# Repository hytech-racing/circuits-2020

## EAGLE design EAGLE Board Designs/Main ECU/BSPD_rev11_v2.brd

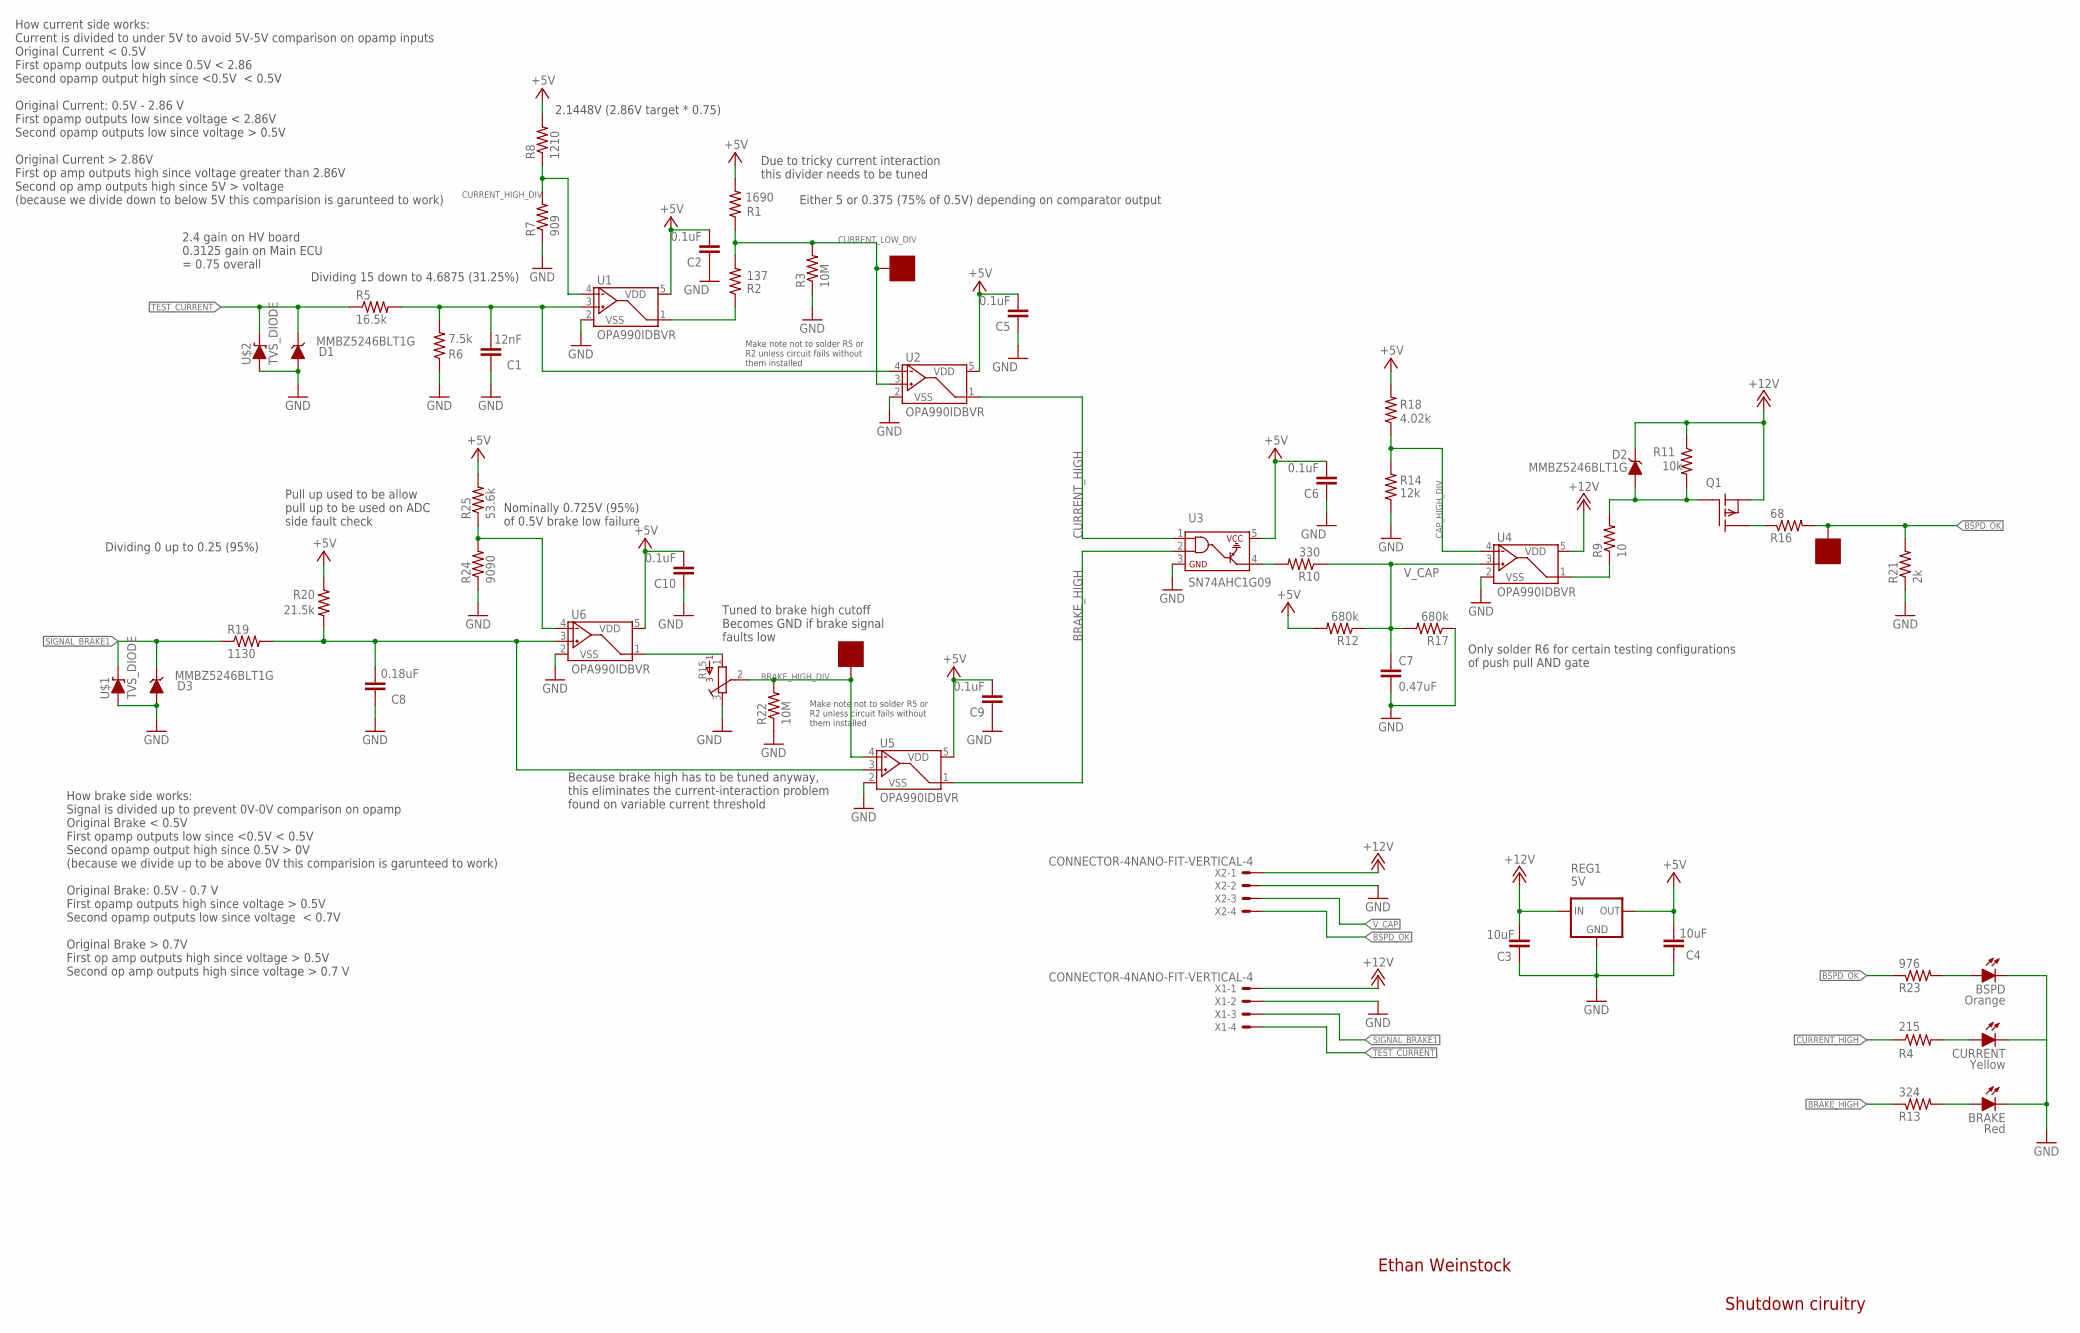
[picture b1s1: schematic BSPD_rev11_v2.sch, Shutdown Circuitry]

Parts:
BRAKE: Red; LED-603
BRAKE_LOW_DIV: SOLDER_PAD; SOLDER_PAD_XSMALL
BSPD: Orange; LED-603
BSPD_OK: SOLDER_PAD; SOLDER_PAD_XSMALL
C1: 12nF; 0603-CAP
C2, C5, C6, C9, C10: 0.1uF; 0603-CAP
C3, C4: 10uF; 0603-CAP
C7: 0.47uF; 0603-CAP
C8: 0.18uF; 0603-CAP
CURRENT: Yellow; LED-603
CURRENT_LOW_DIV: SOLDER_PAD; SOLDER_PAD_XSMALL
D1, D2, D3: MMBZ5246BLT1G; SOT23
Q1: P-CHANNEL_MOSFET_DMP3099L-7; SOT23
R1: 1690; 0603-RES
R2: 137; 0603-RES
R3, R22: 10M; 0603-RES
R4: 215; 0603-RES
R5: 16.5k; 0603-RES
R6: 7.5k; 0603-RES
R7: 909; 0603-RES
R8: 1210; 0603-RES
R9: 10; 0603-RES
R10: 330; 0603-RES
R11: 10k; 0603-RES
R12, R17: 680k; 0603-RES
R13: 324; 0603-RES
R14: 12k; 0603-RES
R15: TRIMPOT_3296C; TRIMPOT_3296
R16: 68; 0603-RES
R18: 4.02k; 0603-RES
R19: 1130; 0603-RES
R20: 21.5k; 0603-RES
R21: 2k; 0603-RES
R23: 976; 0603-RES
R24: 9090; 0603-RES
R25: 53.6k; 0603-RES
REG1: 5V; OKI-78SR
U1, U2, U4, U5, U6: OPA990IDBVR; SOT-23-5
U3: SN74AHC1G09; SOT-23-5
U$1, U$2: TVS_DIODE; U-DFN1608-2
X1, X2: CONNECTOR-4NANO-FIT-VERTICAL-4; NANO-FIT_VERTICAL-4

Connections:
+5V: C2.2, C4.2, C5.2, C6.2, C9.2, C10.2, R1.2, R8.2, R12.2, R18.2, R20.1, R25.2, REG1.3 (OUT), U1.5 (VDD), U2.5 (VDD), U3.5, U5.5 (VDD), U6.5 (VDD)
+12V: C3.2, D2.3 (C), Q1.2 (S), R11.1, REG1.1 (IN), U4.5 (VDD), X1.P$1, X2.P$1
BRAKE_HIGH: R13.1, U3.2, U5.1 (VOUT)
BRAKE_HIGH_DIV: BRAKE_LOW_DIV.P$1, R15.2, R22.2, U5.4 (VIN-)
BSPD_OK: BSPD_OK.P$1, R16.2, R21.2, R23.1, X2.P$4
CAP_HIGH_DIV: R14.2, R18.1, U4.4 (VIN-)
CURRENT_HIGH: R4.1, U2.1 (VOUT), U3.1
CURRENT_HIGH_DIV: R7.2, R8.1, U1.4 (VIN-)
CURRENT_LOW_DIV: CURRENT_LOW_DIV.P$1, R1.1, R2.2, R3.2, U2.3 (VIN+)
GND: BRAKE.C, BSPD.C, C1.1, C2.1, C3.1, C4.1, C5.1, C6.1, C7.2, C8.1, C9.1, C10.1, CURRENT.C, D1.1 (A), D3.1 (A), R3.1, R6.1, R7.1, R14.1, R15.3, R17.1, R21.1, R22.1, R24.1, REG1.2 (GND), U1.2 (VSS), U2.2 (VSS), U3.3, U4.2 (VSS), U5.2 (VSS), U6.2 (VSS), U$1.P$1 (A), U$2.P$1 (A), X1.P$2, X2.P$2
unnamed: Q1.3 (D), R16.1
unnamed: R15.1, U6.1 (VOUT)
unnamed: R9.1, U4.1 (VOUT)
unnamed: C8.2, R19.2, R20.2, U5.3 (VIN+), U6.3 (VIN+)
unnamed: R24.2, R25.1, U6.4 (VIN-)
unnamed: R2.1, U1.1 (VOUT)
unnamed: CURRENT.A, R4.2
unnamed: BRAKE.A, R13.2
unnamed: C1.2, R5.2, R6.2, U1.3 (VIN+), U2.4 (VIN-)
unnamed: R10.2, U3.4
unnamed: BSPD.A, R23.2
unnamed: D2.1 (A), Q1.1 (G), R9.2, R11.2
SIGNAL_BRAKE1: D3.3 (C), R19.1, U$1.P$2 (C), X1.P$3
TEST_CURRENT: D1.3 (C), R5.1, U$2.P$2 (C), X1.P$4
V_CAP: C7.1, R10.1, R12.1, R17.2, U4.3 (VIN+), X2.P$3

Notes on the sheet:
Ethan Weinstock
Shutdown ciruitry
Dividing 15 down to 4.6875 (31.25%)
Either 5 or 0.375 (75% of 0.5V) depending on comparator output
2.1448V (2.86V target * 0.75)
Tuned to brake high cutoff Becomes GND if brake signal faults low
Nominally 0.725V (95%) of 0.5V brake low failure
Dividing 0 up to 0.25 (95%)
2.4 gain on HV board 0.3125 gain on Main ECU = 0.75 overall
Make note not to solder R5 or R2 unless circuit fails without them installed
How current side works: Current is divided to under 5V to avoid 5V-5V comparison on opamp inputs Original Current < 0.5V First opamp outputs low since 0.5V < 2.86 Second opamp output high since <0.5V < 0.5V Original Current: 0.5V - 2.86 V First opamp outputs low since voltage < 2.86V Second opamp o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
Due to tricky current interaction this divider needs to be tuned
Pull up used to be allow pull up to be used on ADC side fault check
Because brake high has to be tuned anyway, this eliminates the current-interaction problem found on variable current threshold
How brake side works: Signal is divided up to prevent 0V-0V comparison on opamp Original Brake < 0.5V First opamp outputs low since <0.5V < 0.5V Second opamp output high since 0.5V > 0V (because we divide up to be above 0V this comparision is garunteed to work) Original Brake: 0.5V - 0.7 V First op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
Only solder R6 for certain testing configurations of push pull AND gate

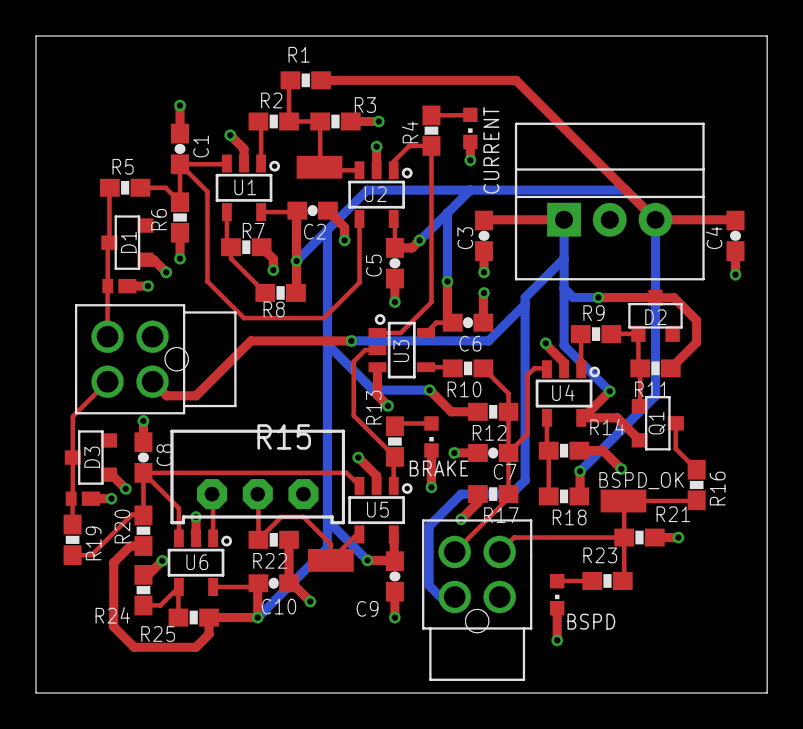
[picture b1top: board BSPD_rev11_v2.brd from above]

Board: 2 copper layers, 40.6 x 36.5 mm, 56 parts (0 on the bottom side), 25 nets.

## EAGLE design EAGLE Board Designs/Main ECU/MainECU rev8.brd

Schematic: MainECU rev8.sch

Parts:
5ABOARDFUSE, 5AFUSE, 5ASHUTDOWNFUSE: FUSE_MINIBLADE; MINI-BLADE_FUSE_HOLDER
ACC1_PD, ACC1_PU, ACC2_PD, ACC2_PU: 10k; 0805
ADXL345_BREAKOUT: M09; 1X09
BMS_SHUTDOWN_RLY: RT424012; RELAY_DPDT
BOARD_TEMP: THERMISTOR_NCP210805; 0805
BRAKE_PU: 10k; 0805
C1, C2, C20, C21: 10uF; 0805
C3, C14, C17: 1nF; 0805
C4, C12, C15, C16, C18, C19, C22, C23, C25, C26, C32, C34, C36, C43, C44, C45: .1uF; 0805
C5, C6, C11, C31, C33, C35, C37, C42: 1uF; 0805
C7, C8: 47nF; 0805
C9, C10, C30, C38, C39: 0.1uF; 0805
C13, C24: 470pF; 0805
C27, C28, C29: CAP0805; 0805
C40: 470uF; CAP-PTH-LARGE
C41: 4.7nF; 0805
CAN_TERM_JMP: M02_SLIM; 1X02_SLIM
CAN_TRANSCEIVER, CAN_TRANSCEIVER1: MCP2551; SOIC-08
D1, D2, D3, D4, D5, D6, D7, D13, D15, D16, D19, D20, D21, D22: TS4148 RYG; 0805_D
D8, D9, D10, D11, D12, D14: MMBZ5246BLT1G; SOT23
IMD_SHUTDOWN_RLY: RT424009; RELAY_DPDT
INVERTER_PWR_RELAY: G5LE; ZF112
J1, J2, J3, J4, J5, J6, J7, J8: JUMPER; 0805
LED1: White; LED-805
LED2: RED; LED-805
LED3, LED7, LED11: Green; LED-805
LED4, LED6, LED10, LED12, LED13: Red; LED-805
LED5, LED9: Yellow; LED-805
LED8: Purple; LED-805
LED14: Blue; LED-805
LED15: YELLOW; LED-805
LED16: GREEN; LED-805
MTK3339_BREAKOUT: M09; 1X09
P1, P2: SOLDER_PAD; SOLDER_PAD_XSMALL
Q9, Q11: DMG3406LSOT; SOT23
Q12: P-CHANNEL_MOSFET_DMP3099L-7; SOT23
R1, R3: 1K; 0805
R2, R4: 2K; 0805
R5, R7, R11, R15, R23, R57, R59, R61: 43k; 0805
R6, R8, R21, R22, R29, R58, R60, R62: 12k; 0805
R9, R10, R24, R27, R28, R47, R48, R53: 10k; 0805
R12, R14, R18, R55: 2k; 0805
R13, R63: 20; 0805
R16, R25, R32, R51, R52: 1.2k; 0805
R17: 20k; 0805
R20, R67, R68: 270; 0805
R30, R56: 33; 0805
R33, R34: 4.7k; 0805
R35, R36, R38, R39, R40, R41, R42, R43: 150; 0805
R37, R44, R45: 0; 0805
R46, R49: 60; 0805
R54: 5.1k; 0805
R64, R65, R66: RESISTOR0805-RES; 0805
R69: 200; 0805
REG, REG3: 5V; OKI-78SR
REG1: LM3940; SOT223
S1: BTN_10-XXSMD; TACTILE_SWITCH_SMD_6.2MM_TALL
U$1: TEENSY_3.2_SIMPLE
U$2: TEENSY_3.5_EXT
U$3: XBEE
U$4, U$6, U$7: N-CHANNEL_MOSFET_IRF1324PBF; TO-220-H-HOLE
U$5, U$19: MC34152; SOIC-08
U$8, U$11, U$12, U$14, U$15: TEST_POINT
U$9, U$10: ACS715_CURRENT_SENSOR; SOP8
U$13: CDSOT23-T24CAN-Q; SOT23
U$16: CR-2450/G1AN
U$17: MCP23S17SSOP28; SSOP28
U$18: MCP3208SOIC; SOIC-16
U$20, U$23, U$24: MCP6002SOIC; SOIC-08
U$21, U$22, U$26, U$27, U$28: MAX7480; SOIC-08
U$25: TXB0104TSSOP; TSSOP-14
U$29, U$30: TLP291-4; 11-11F1
U$31: RT424009; RELAY_DPDT
X1: CONNECTOR-37; AUTOSPORT_14-35
X2: CONNECTOR-4AUTOSPORT; AUTOSPORT_12-04
X3, X4: CONNECTOR-4NANO-FIT-VERTICAL-4; NANO-FIT_VERTICAL-4

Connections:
3.3V: R33.2, R34.2, U$2.3.3V
3.3V_MAIN_TEENSY: C44.1, U$1.3.3V, U$25.1 (VCCA), U$25.8 (OE)
12VIN: U$9.1 (IP+), U$9.2 (IP+), X2.P$1
12VSUPPLY_DIV: C37.2, R23.2, R29.1, U$23.3 (VINA+)
12VSUPPLY_READ: U$18.4 (CH3), U$23.1 (VOUTA), U$23.2 (VINA-)
12VUNFUSED: 5ABOARDFUSE.L1 (1), 5ABOARDFUSE.L2 (1), 5ASHUTDOWNFUSE.L1 (1), 5ASHUTDOWNFUSE.L2 (1), U$9.3 (IP-), U$9.4 (IP-)
+5V: ACC1_PU.2, ACC2_PU.2, BOARD_TEMP.1, BRAKE_PU.2, C2.2, C4.1, C11.2, C15.1, C18.1, C30.2, C31.2, C32.2, C33.2, C34.2, C35.1, C36.1, C38.1, C45.1, CAN_TRANSCEIVER1.3, R20.1, R54.1, REG.3 (OUT), U$1.VIN, U$11.P$1, U$17.9 (VDD), U$17.18 (!RESET), U$18.15 (VREF), U$18.16 (VDD), U$23.8 (VDD), U$24.8 (VDD), U$25.14 (VCCB), U$26.4 (VDD), U$26.7 (!SHDN), U$27.4 (VDD), U$27.7 (!SHDN), U$28.4 (VDD), U$28.7 (!SHDN), X1.P$27, X1.P$28, X1.P$29
BMS_OK_READ: R7.2, R8.1, U$18.6 (CH5)
BMS_PWR_STEP: BMS_SHUTDOWN_RLY.3, BMS_SHUTDOWN_RLY.COIL-, D5.A, D16.A
BRAKE_LIGHT: Q12.3 (D), X1.P$9
BRAKE_LIGHT_CTRL: D12.3 (C), Q11.1 (G), R10.2, U$1.D7(RX3)
CANH: CAN_TERM_JMP.1, CAN_TRANSCEIVER.7, CAN_TRANSCEIVER1.7, U$13.2, X1.P$12, X1.P$13, X3.P$4, X4.P$4
CANL: CAN_TRANSCEIVER.6, CAN_TRANSCEIVER1.6, R49.1, U$13.1, X1.P$11, X1.P$26, X3.P$3, X4.P$3
COOLINGSENSE: J5.2, R3.2, R4.2, U$20.3 (VINA+)
COOLINGSENSE_FILT: J5.1, U$2.A12, U$22.5 (OUT)
CS1_5V: U$18.10 (!CS!/SHDN), U$25.13 (B1)
CS1_TEENSY: U$1.D9(RX2), U$25.2 (A1)
CS2_5V: U$17.11 (!CS), U$25.12 (B2)
CS2_TEENSY: U$1.D10(TX2), U$25.3 (A2)
CURRENTSENSE2: C27.2, C28.2, C29.2, U$4.3 (S), U$6.3 (S), U$7.3 (S), U$10.1 (IP+), U$10.2 (IP+)
DASH11_READ: R11.2, R21.1, U$1.A0
DASH12_READ: R57.2, R58.1, U$1.A1
DASH_1_EXTERN: R44.2, X1.P$1
DASH_1_INTER: R35.1, U$17.1 (GPB0)
DASH_2_EXTERN: R37.2, X1.P$2
DASH_2_INTER: R36.1, U$17.2 (GPB1)
DASH_3_EXTERN: U$29.11 (EM3), X1.P$3
DASH_3_INTER: R38.1, U$17.3 (GPB2)
DASH_4_EXTERN: U$29.9 (EM4), X1.P$4
DASH_4_INTER: R39.1, U$17.4 (GPB3)
DASH_5_EXTERN: J1.1, U$30.15 (EM1), X1.P$18
DASH_5_INTER: J1.2, R40.1, U$17.5 (GPB4)
DASH_6_EXTERN: J2.1, U$30.13 (EM2), X1.P$19
DASH_6_INTER: J2.2, R41.1, U$17.6 (GPB5)
DASH_7_EXTERN: J3.1, U$30.11 (EM3), X1.P$20
DASH_7_INTER: J3.2, R42.1, U$17.7 (GPB6)
DASH_8_EXTERN: J4.1, U$30.9 (EM4), X1.P$21
DASH_8_INTER: J4.2, R43.1, U$17.8 (GPB7)
DASH_9_EXTERN: U$17.21 (GPA0), X1.P$23
DASH_10_EXTERN: U$17.22 (GPA1), X1.P$32
DASH_11_EXTERN: D19.A, J7.1, X1.P$6
DASH_11_INTER: J7.2, U$17.23 (GPA2)
DASH_12_EXTERN: D20.A, J8.1, X1.P$22
DASH_12_INTER: J8.2, U$17.24 (GPA3)
ECUSENSE: J6.2, R1.2, R2.2, U$20.5 (VINB+)
ECUSENSE_FILT: J6.1, U$2.A13, U$21.5 (OUT)
FAN1-: 5AFUSE.R1 (2), 5AFUSE.R2 (2), R65.1, U$7.2 (D)
FAN1CONTROL: LED4.A, U$1.A8, U$5.2 (IN_A)
FAN1DRIVE: D9.3 (C), R24.2, U$5.7 (OUT_A), U$7.1 (G)
FAN2-: R64.1, U$4.2 (D), X2.P$3
FAN2CONTROL: LED13.A, U$1.A9, U$5.4 (IN_B)
FAN2DRIVE: D8.3 (C), R28.2, U$4.1 (G), U$5.5 (OUT_B)
IMD_PWR_STEP: D6.A, D15.A, IMD_SHUTDOWN_RLY.3, IMD_SHUTDOWN_RLY.COIL-
INVERTER_CTRL: D14.3 (C), Q9.1 (G), R16.1, R47.1, U$1.D6
INVERTER_SUPPLY: INVERTER_PWR_RELAY.S, X1.P$7
LATCH_EXT_BUTTON: D13.C, D15.C, D16.C, LED1.C, S1.A1, S1.A2 (P1), X1.P$37
MISO_TEENSY: U$1.D12, U$17.14 (SO), U$18.12 (DOUT)
MOSI_5V: U$17.13 (SI), U$18.11 (DIN), U$25.10 (B4)
MOSI_TEENSY: U$1.D11, U$25.5 (A4)
MTK3339_DIN: MTK3339_BREAKOUT.6, U$2.D1(TX1)
MTK3339_DOUT: MTK3339_BREAKOUT.5, U$2.D0(RX1)
MTK3339_FIX: MTK3339_BREAKOUT.4, U$2.D2
unnamed: 5AFUSE.L1 (1), 5AFUSE.L2 (1), X1.P$17
unnamed: LED1.A, R54.2
unnamed: R1.1, U$9.7 (VIOUT)
unnamed: C12.2, U$27.1 (COM), U$27.6 (OS)
unnamed: D20.C, R57.1
unnamed: R3.1, U$10.7 (VIOUT)
unnamed: MTK3339_BREAKOUT.2, R53.2
unnamed: C8.1, U$9.6 (FILTER)
unnamed: LED3.A, R56.2
unnamed: D1.C, R5.1
unnamed: D2.C, R7.1
unnamed: CAN_TRANSCEIVER.4, U$2.D4(CANRX)
unnamed: CAN_TRANSCEIVER.1, U$2.D3(CANTX)
unnamed: CAN_TRANSCEIVER1.4, U$1.D4(CANRX)
unnamed: CAN_TERM_JMP.2, R46.2
unnamed: D19.C, R11.1
unnamed: LED5.A, R14.2
unnamed: U$20.1 (VOUTA), U$20.2 (VINA-), U$22.2 (IN)
unnamed: C3.1, U$27.8 (CLK)
unnamed: CAN_TRANSCEIVER1.1, U$1.D3(CANTX)
unnamed: U$24.1 (VOUTA), U$24.2 (VINA-), U$28.2 (IN)
unnamed: U$24.6 (VINB-), U$24.7 (VOUTB), U$27.2 (IN)
unnamed: U$23.6 (VINB-), U$23.7 (VOUTB), U$26.2 (IN)
unnamed: LED9.A, R55.2
unnamed 89: D7.A, D13.A, U$31.3, U$31.COIL-; also elsewhere on the board
unnamed: LED6.A, R16.2
unnamed: LED8.A, R20.2
unnamed: R36.2, U$29.3 (VCC2)
unnamed: D21.C, R59.1
unnamed: LED7.A, R17.2
unnamed: D3.C, R15.1
unnamed: D22.C, R61.1
unnamed: LED14.C, R45.2
unnamed: C16.2, U$28.1 (COM), U$28.6 (OS)
unnamed: C19.2, U$26.1 (COM), U$26.6 (OS)
unnamed: C14.1, U$28.8 (CLK)
unnamed: U$20.6 (VINB-), U$20.7 (VOUTB), U$21.2 (IN)
unnamed: C17.1, U$26.8 (CLK)
unnamed: R37.1, U$29.13 (EM2)
unnamed: C23.2, U$21.1 (COM), U$21.6 (OS)
unnamed: C13.1, U$21.8 (CLK)
unnamed: LED11.C, R30.2
unnamed: LED11.A, U$3.6 (PWM0/RSSI)
unnamed: C7.1, U$10.6 (FILTER)
unnamed: LED10.A, U$3.15 (ASC/AD5/DIO5)
unnamed: LED10.C, R32.2
unnamed: R35.2, U$29.1 (VCC1)
unnamed: R38.2, U$29.5 (VCC3)
unnamed: R39.2, U$29.7 (VCC4)
unnamed: R40.2, U$30.1 (VCC1)
unnamed: R41.2, U$30.3 (VCC2)
unnamed: R42.2, U$30.5 (VCC3)
unnamed: R43.2, U$30.7 (VCC4)
unnamed: D11.1 (A), Q11.3 (D), Q12.1 (G), R48.2
unnamed: R44.1, U$29.15 (EM1)
unnamed: U$2.GND_2, U$16.-
unnamed: C41.1, R46.1, R49.2
unnamed: LED14.A, U$3.20 (AD0/DIO0)
unnamed: C27.1, R64.2
unnamed: D4.A, INVERTER_PWR_RELAY.2 (COIL-), Q9.3 (D)
unnamed: C26.2, U$22.1 (COM), U$22.6 (OS)
unnamed: C24.1, U$22.8 (CLK)
unnamed: LED4.C, R25.1
unnamed: LED12.C, R51.1
unnamed: LED13.C, R52.1
unnamed: P1.P$1, U$17.25 (GPA4)
unnamed: P2.P$1, U$17.26 (GPA5)
unnamed: C28.1, R65.2
unnamed: C29.1, R66.2
unnamed: LED2.C, R67.2
unnamed: LED15.C, R68.2
unnamed: LED16.C, R69.2
OKHS_READ: R5.2, R6.1, U$18.7 (CH6)
PUMP1-: R66.1, U$6.2 (D), X2.P$2
PUMPCONTROL: LED12.A, U$1.A6, U$19.2 (IN_A)
PUMPDRIVE: D10.3 (C), R27.2, U$6.1 (G), U$19.7 (OUT_A)
READ_ACCEL1: U$18.2 (CH1), U$27.5 (OUT)
READ_ACCEL2: U$18.3 (CH2), U$28.5 (OUT)
READ_BRAKE: U$18.1 (CH0), U$26.5 (OUT)
SCK_5V: U$17.12 (SCK), U$18.13 (CLK), U$25.11 (B3)
SCK_TEENSY: U$1.D13, U$25.4 (A3)
SCL: ADXL345_BREAKOUT.9, R34.1, U$2.A5
SDA: ADXL345_BREAKOUT.8, R33.1, U$2.A4
SHUTDOWN_A: 5ASHUTDOWNFUSE.R1 (2), 5ASHUTDOWNFUSE.R2 (2), IMD_SHUTDOWN_RLY.6
SHUTDOWN_B: BMS_SHUTDOWN_RLY.6, D21.A, IMD_SHUTDOWN_RLY.5, R14.1
SHUTDOWN_B_READ: R59.2, R60.1, U$1.A2
SHUTDOWN_C: BMS_SHUTDOWN_RLY.5, D22.A, R17.1, U$31.6; also elsewhere on the board
SHUTDOWN_C_READ: R61.2, R62.1, U$1.A3
SHUTDOWN_D: D3.A, U$31.5, X1.P$5; also elsewhere on the board
SHUTDOWN_OUT_READ: R15.2, R22.1, U$18.5 (CH4)
SIGNAL_ACCEL1: ACC1_PD.1, ACC1_PU.1, U$24.5 (VINB+), X1.P$25
SIGNAL_ACCEL2: ACC2_PD.1, ACC2_PU.1, U$24.3 (VINA+), X1.P$24
SIGNAL_BRAKE: BRAKE_PU.1, U$14.P$1, U$23.5 (VINB+), X1.P$8
SOFTWARE_SHUTDOWN: D13.3, U$1.A7; also elsewhere on the board
TELEMETRY5V: ADXL345_BREAKOUT.1, C5.1, C9.1, C10.1, C21.2, C22.1, C25.1, C42.2, C43.2, CAN_TRANSCEIVER.3, MTK3339_BREAKOUT.8, R53.1, REG1.1 (IN), REG3.3 (OUT), U$2.VIN, U$9.8 (VCC), U$10.8 (VCC), U$20.8 (VDD), U$21.4 (VDD), U$21.7 (!SHDN), U$22.4 (VDD), U$22.7 (!SHDN)
TEMPSENSE: BOARD_TEMP.2, R9.2, U$18.8 (CH7)
VBAT_RTC: MTK3339_BREAKOUT.3, U$2.VBAT, U$16.+_0 (+), U$16.+_1 (+)
VCC: C6.2, C39.1, REG1.3 (OUT), U$3.1 (VCC)
XB8: U$2.D7(RX3), U$3.4 (DO8)
XBDI: U$2.D10(TX2), U$3.3 (DIN)
XBDO: U$2.D9(RX2), U$3.2 (DOUT)

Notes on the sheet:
ECU Current Sensor
Cooling Current Sensor
Pullup/down resistors to detect open circuit. Install only one per signal on ACCEL1 and ACCEL2.
Pedals 5V
CANL for Motor Controller
1nF for 530Hz filter
12V for Dash
Dash 5, 6, 7, 8 Can be inputs or outputs For input, solder jumper. For output, solder resistor (R40-R43).
470pF for ~1kHz filter (1.13kHz)
Install resistors or LEDs here to limit current or drop voltage
WARNING: INSTALL ONLY JUMPER (J1-J4) OR RESISTOR (R40-R43) ON DASH CHANNELS 5-8. DO NOT INSTALL BOTH ON SINGLE CHANNEL
Alternate stocked: NCP18XV103J0SRB
Install jumpers above to bypass optional filter circuit to left WARNING: INSTALL ONLY JUMPERS (J5-J6) OR FILTER CIRCUIT
To configure Dash 11 or 12 as 5V input/output, solder jumper (J5 or J6). If configuring as 12V input, do not solder jumper.
WARNING: DO NOT INSTALL JUMPER (J5 OR J6) IF CONNECTING CHANNEL 11 OR 12 TO >5V SIGNAL.
Choose Resistor (R64-R66) and Capacitor (C27-C29) values based on measured spikes and circuit behavior

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
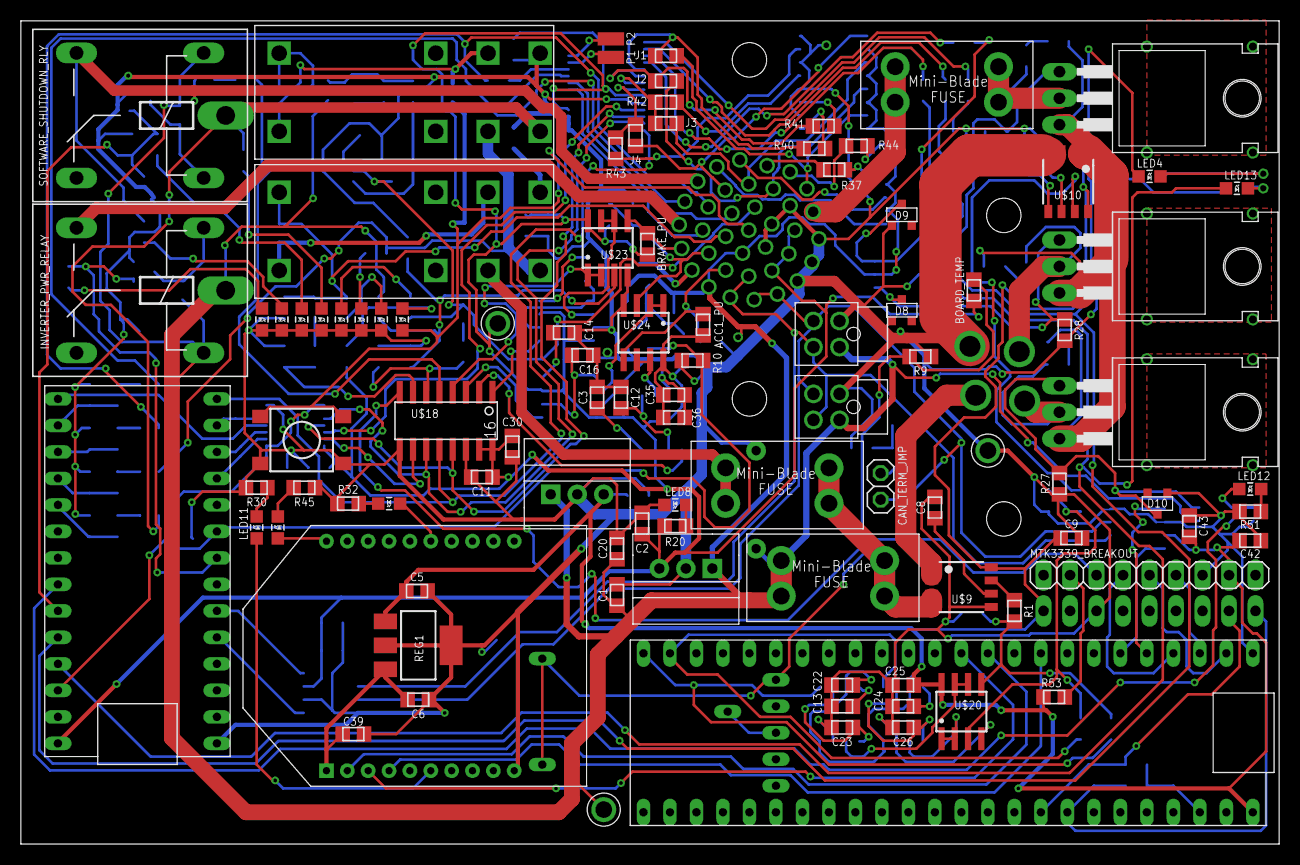
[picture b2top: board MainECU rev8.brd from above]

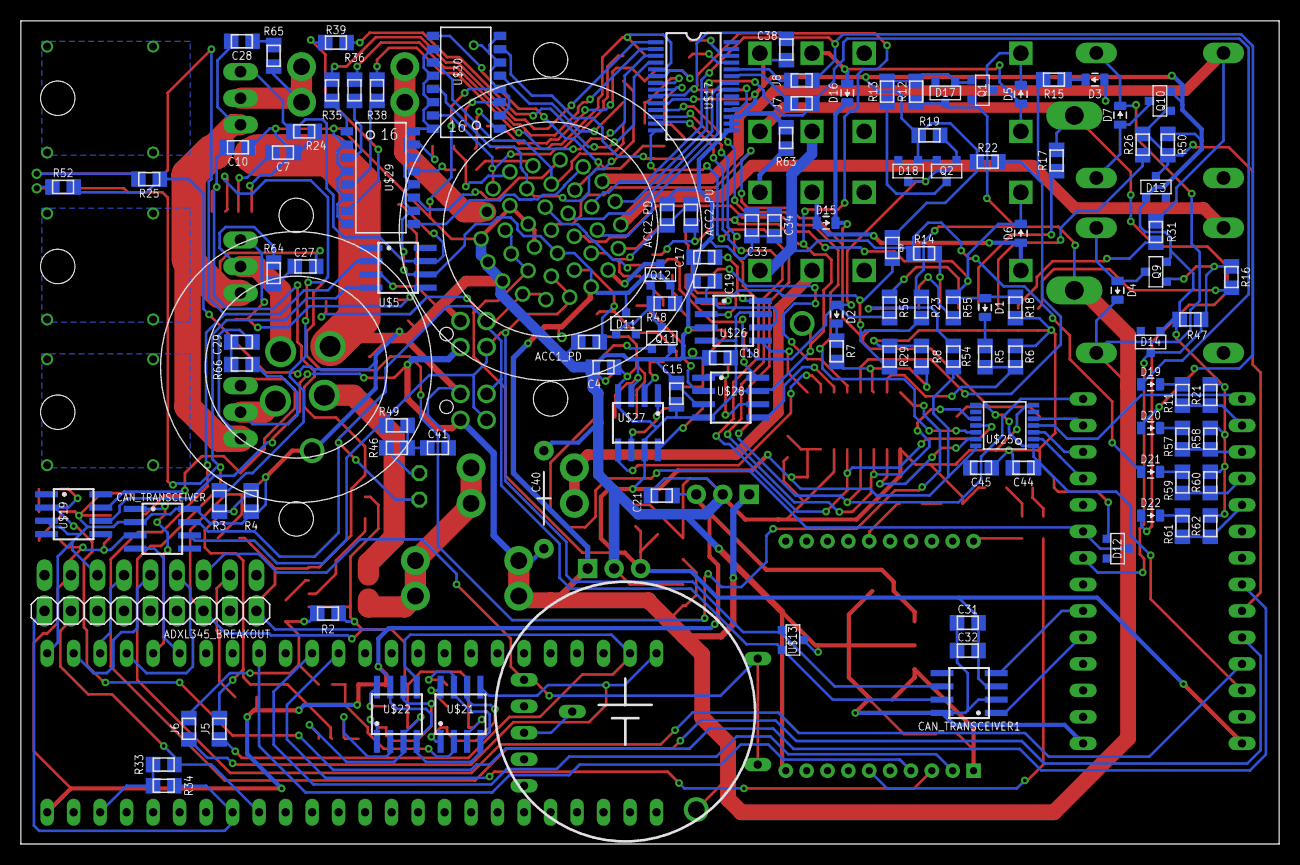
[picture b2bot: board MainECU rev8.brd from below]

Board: 4 copper layers, 120.6 x 78.9 mm, 218 parts (120 on the bottom side), 170 nets.

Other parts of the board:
D17, D18: MMBZ5246BLT1G; SOT23
LED17, LED18: Red; LED-805
Q1: P-CHANNEL_MOSFET_DMP3099L-7; SOT23
Q2, Q10: SOT23
R19, R50: 10k; 0805
R26: 1.2K; 0805
R31: 6.8k; 0805
SOFTWARE_SHUTDOWN_RLY: G5LE; ZF112

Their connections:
unnamed 89: Q10.3, SOFTWARE_SHUTDOWN_RLY.1; also elsewhere on the board
unnamed: LED18.A, R31.2
unnamed: LED17.A, R26.2
SHUTDOWN_C: SOFTWARE_SHUTDOWN_RLY.P; also elsewhere on the board
SHUTDOWN_D: R31.1, SOFTWARE_SHUTDOWN_RLY.S; also elsewhere on the board
SOFTWARE_SHUTDOWN: Q10.1, R26.1, R50.1; also elsewhere on the board

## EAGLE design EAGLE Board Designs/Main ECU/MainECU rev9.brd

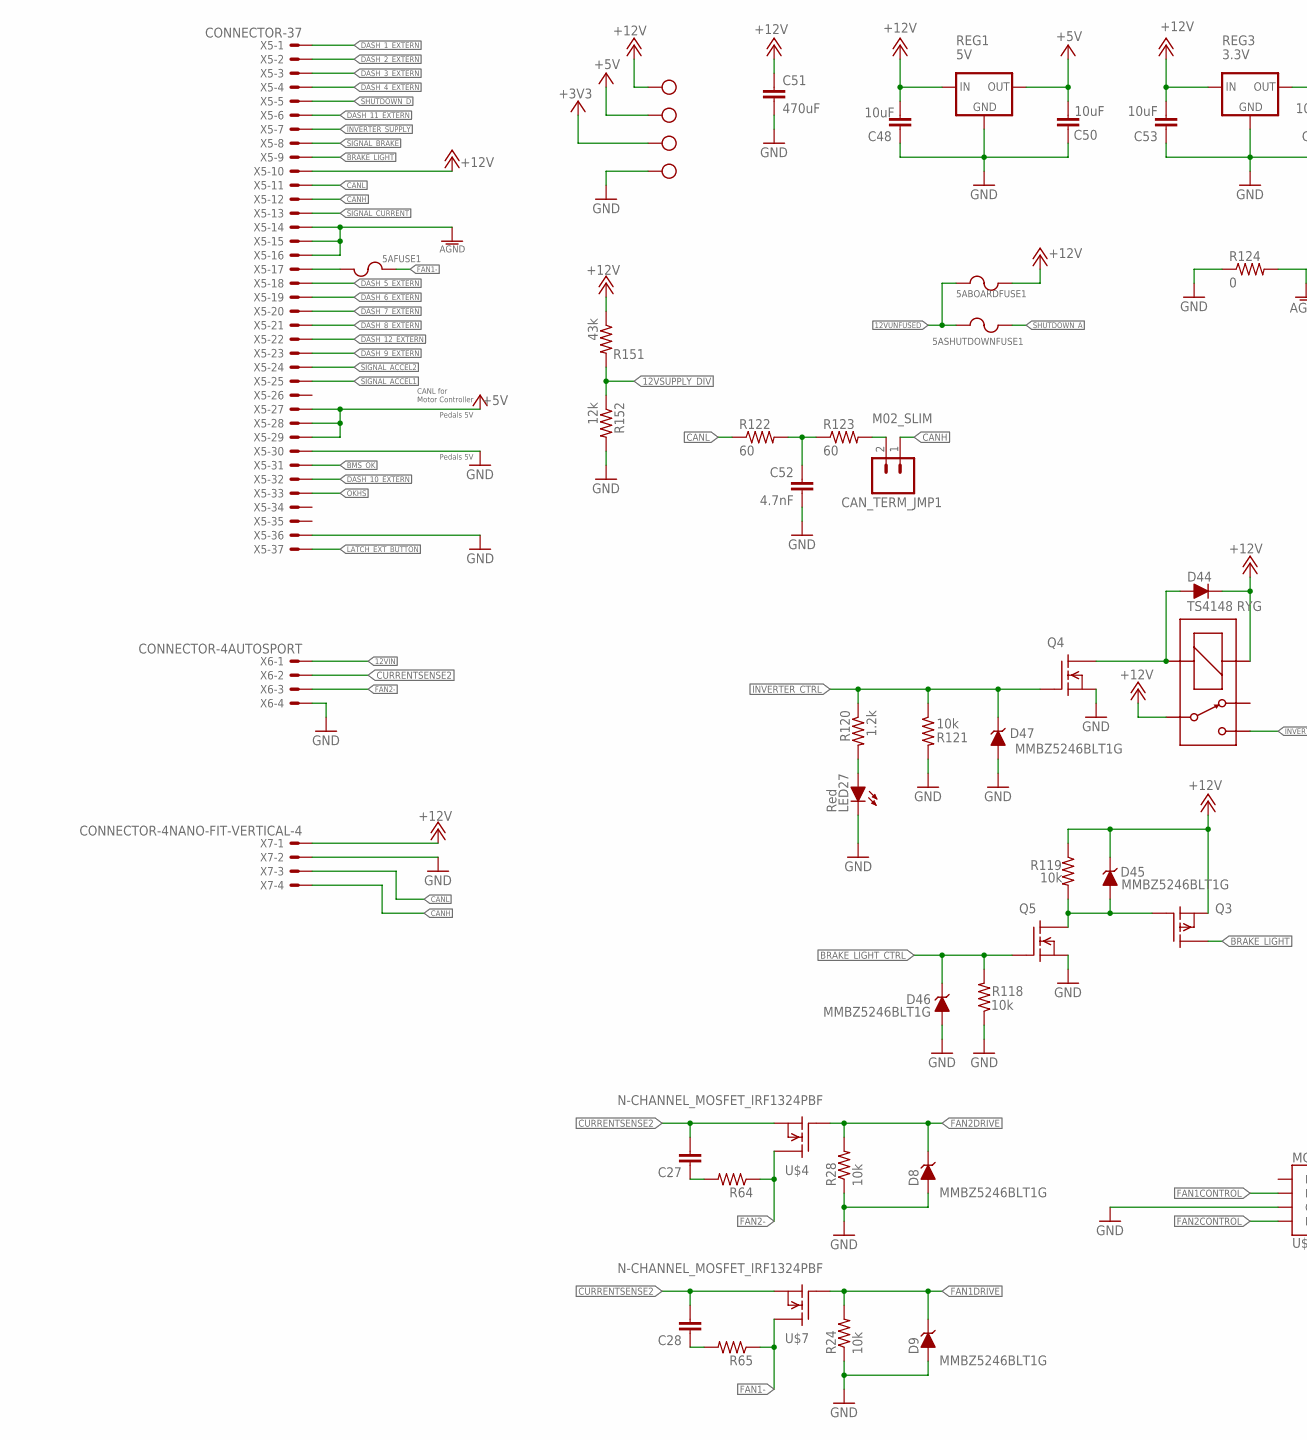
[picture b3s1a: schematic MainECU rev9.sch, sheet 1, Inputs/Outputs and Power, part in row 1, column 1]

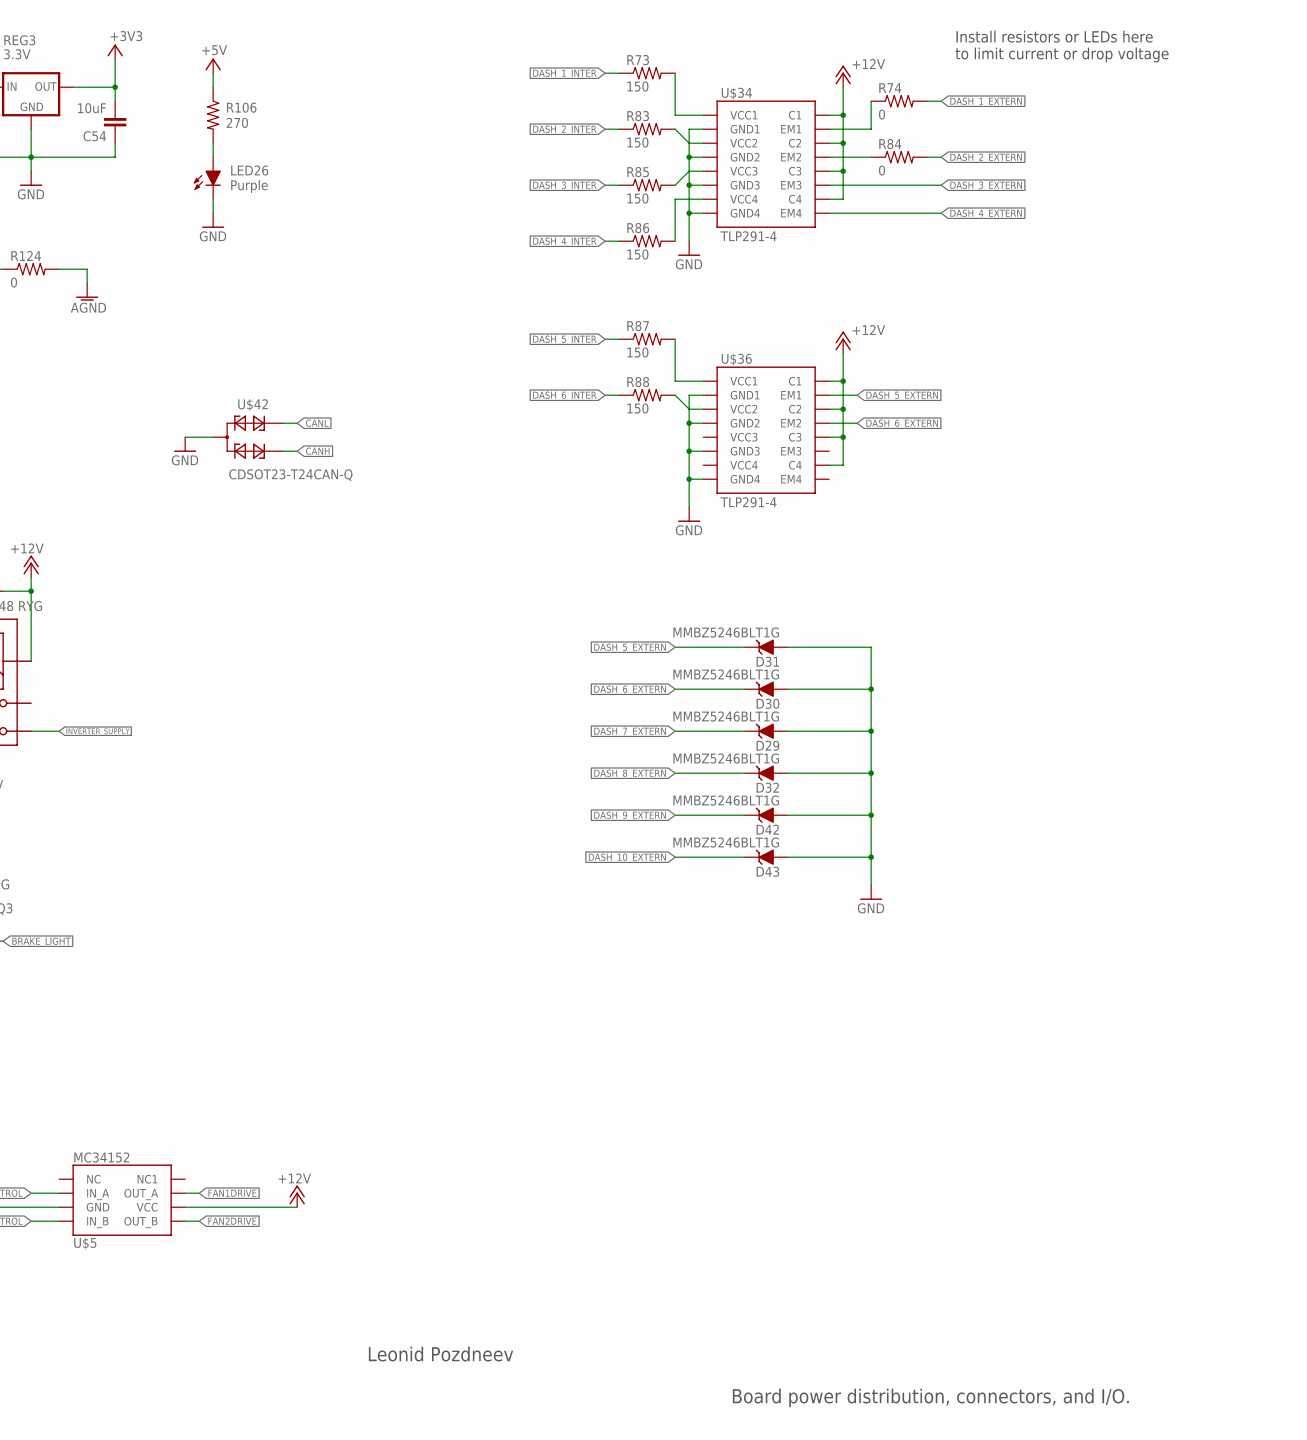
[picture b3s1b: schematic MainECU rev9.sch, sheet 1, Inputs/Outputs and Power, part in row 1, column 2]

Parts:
3V3_TEST: TEST_POINT
5ABOARDFUSE1, 5AFUSE1, 5ASHUTDOWNFUSE1: FUSE_MINIBLADE; MINI-BLADE_FUSE_HOLDER
C: 12V_TEST; TEST_POINT
C27, C28: CAP0603-CAP; 0603-CAP
C48, C50, C53, C54: 10uF; 0603-CAP
C51: 470uF; CAP-PTH-LARGE
C52: 4.7nF; 0603-CAP
CAN_TERM_JMP1: M02_SLIM; 1X02_SLIM
D8, D9, D29, D30, D31, D32, D42, D43, D45, D46, D47: MMBZ5246BLT1G; SOT23
D44: TS4148 RYG; 0805_D
INVERTER_PWR_RELAY1: G5LE; ZF112
LED26: Purple; LED-805
LED27: Red; LED-805
Q3: P-CHANNEL_MOSFET_DMP3099L-7; SOT23
Q4, Q5: DMG3406LSOT; SOT23
R24, R28, R118, R119, R121: 10k; 0603-RES
R64, R65: RESISTOR0603; 0603-RES
R73, R83, R85, R86, R87, R88: 150; 0603-RES
R74, R84, R124: 0; 0603-RES
R106: 270; 0603-RES
R120: 1.2k; 0603-RES
R122, R123: 60; 0603-RES
R151: 43k; 0603-RES
R152: 12k; 0603-RES
REG1: 5V; OKI-78SR
REG3: 3.3V; OKI-78SR
U$4, U$7: N-CHANNEL_MOSFET_IRF1324PBF; TO-220-H-HOLE
U$5: MC34152; SOIC-08
U$15, U$19: TEST_POINT
U$34, U$36: TLP291-4; 11-11F1
U$42: CDSOT23-T24CAN-Q; SOT23
X5: CONNECTOR-37; AUTOSPORT_14-35
X6: CONNECTOR-4AUTOSPORT; AUTOSPORT_12-04
X7: CONNECTOR-4NANO-FIT-VERTICAL-4; NANO-FIT_VERTICAL-4

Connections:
12VIN: X6.P$1; also elsewhere on the board
12VSUPPLY_DIV: R151.2, R152.1; also elsewhere on the board
12VUNFUSED: 5ABOARDFUSE1.L1 (1), 5ABOARDFUSE1.L2 (1), 5ASHUTDOWNFUSE1.L1 (1), 5ASHUTDOWNFUSE1.L2 (1); also elsewhere on the board
+3V3: 3V3_TEST.P$1, C54.2, REG3.3 (OUT); also elsewhere on the board
+5V: C50.2, R106.1, REG1.3 (OUT), U$15.P$1, X5.P$27, X5.P$28, X5.P$29; also elsewhere on the board
+12V: 5ABOARDFUSE1.R1 (2), 5ABOARDFUSE1.R2 (2), C.P$1, C48.2, C51.1, C53.2, D44.C, D45.3 (C), INVERTER_PWR_RELAY1.1 (COIL+), INVERTER_PWR_RELAY1.P, Q3.2 (S), R119.1, R151.1, REG1.1 (IN), REG3.1 (IN), U$5.6 (VCC), U$34.10 (C4), U$34.12 (C3), U$34.14 (C2), U$34.16 (C1), U$36.10 (C4), U$36.12 (C3), U$36.14 (C2), U$36.16 (C1), X5.P$10, X7.P$1; also elsewhere on the board
AGND: R124.2, X5.P$14, X5.P$15, X5.P$16; also elsewhere on the board
BMS_OK: X5.P$31; also elsewhere on the board
BRAKE_LIGHT: Q3.3 (D), X5.P$9
BRAKE_LIGHT_CTRL: D46.3 (C), Q5.1 (G), R118.2; also elsewhere on the board
CANH: CAN_TERM_JMP1.1, U$42.2, X5.P$12, X7.P$4; also elsewhere on the board
CANL: R122.1, U$42.1, X5.P$11, X7.P$3; also elsewhere on the board
CURRENTSENSE2: C27.2, C28.2, U$4.3 (S), U$7.3 (S), X6.P$2; also elsewhere on the board
DASH_1_EXTERN: R74.2, X5.P$1
DASH_1_INTER: R73.1; also elsewhere on the board
DASH_2_EXTERN: R84.2, X5.P$2
DASH_2_INTER: R83.1; also elsewhere on the board
DASH_3_EXTERN: U$34.11 (EM3), X5.P$3
DASH_3_INTER: R85.1; also elsewhere on the board
DASH_4_EXTERN: U$34.9 (EM4), X5.P$4
DASH_4_INTER: R86.1; also elsewhere on the board
DASH_5_EXTERN: D31.3 (C), U$36.15 (EM1), X5.P$18
DASH_5_INTER: R87.1; also elsewhere on the board
DASH_6_EXTERN: D30.3 (C), U$36.13 (EM2), X5.P$19
DASH_6_INTER: R88.1; also elsewhere on the board
DASH_7_EXTERN: D29.3 (C), X5.P$20; also elsewhere on the board
DASH_8_EXTERN: D32.3 (C), X5.P$21; also elsewhere on the board
DASH_9_EXTERN: D42.3 (C), X5.P$23; also elsewhere on the board
DASH_10_EXTERN: D43.3 (C), X5.P$32; also elsewhere on the board
DASH_11_EXTERN: X5.P$6; also elsewhere on the board
DASH_12_EXTERN: X5.P$22; also elsewhere on the board
FAN1-: 5AFUSE1.R1 (2), 5AFUSE1.R2 (2), R65.1, U$7.2 (D)
FAN1CONTROL: U$5.2 (IN_A); also elsewhere on the board
FAN1DRIVE: D9.3 (C), R24.2, U$5.7 (OUT_A), U$7.1 (G)
FAN2-: R64.1, U$4.2 (D), X6.P$3
FAN2CONTROL: U$5.4 (IN_B); also elsewhere on the board
FAN2DRIVE: D8.3 (C), R28.2, U$4.1 (G), U$5.5 (OUT_B)
GND: C48.1, C50.1, C51.2, C52.2, C53.1, C54.1, D8.1 (A), D9.1 (A), D29.1 (A), D30.1 (A), D31.1 (A), D32.1 (A), D42.1 (A), D43.1 (A), D46.1 (A), D47.1 (A), LED26.C, LED27.C, Q4.2 (S), Q5.2 (S), R24.1, R28.1, R118.1, R121.2, R124.1, R152.2, REG1.2 (GND), REG3.2 (GND), U$5.3 (GND), U$19.P$1, U$34.2 (GND1), U$34.4 (GND2), U$34.6 (GND3), U$34.8 (GND4), U$36.2 (GND1), U$36.4 (GND2), U$36.6 (GND3), U$36.8 (GND4), U$42.3, X5.P$30, X5.P$36, X6.P$4, X7.P$2; also elsewhere on the board
INVERTER_CTRL: D47.3 (C), Q4.1 (G), R120.1, R121.1; also elsewhere on the board
INVERTER_SUPPLY: INVERTER_PWR_RELAY1.S, X5.P$7
LATCH_EXT_BUTTON: X5.P$37; also elsewhere on the board
unnamed: C27.1, R64.2
unnamed: 5AFUSE1.L1 (1), 5AFUSE1.L2 (1), X5.P$17
unnamed: C28.1, R65.2
unnamed: R73.2, U$34.1 (VCC1)
unnamed: R74.1, U$34.15 (EM1)
unnamed: R83.2, U$34.3 (VCC2)
unnamed: R84.1, U$34.13 (EM2)
unnamed: R85.2, U$34.5 (VCC3)
unnamed: R86.2, U$34.7 (VCC4)
unnamed: R87.2, U$36.1 (VCC1)
unnamed: R88.2, U$36.3 (VCC2)
unnamed: LED26.A, R106.2
unnamed: D45.1 (A), Q3.1 (G), Q5.3 (D), R119.2
unnamed: LED27.A, R120.2
unnamed: D44.A, INVERTER_PWR_RELAY1.2 (COIL-), Q4.3 (D)
unnamed: CAN_TERM_JMP1.2, R123.2
unnamed: C52.1, R122.2, R123.1
OKHS: X5.P$33; also elsewhere on the board
SHUTDOWN_A: 5ASHUTDOWNFUSE1.R1 (2), 5ASHUTDOWNFUSE1.R2 (2); also elsewhere on the board
SHUTDOWN_D: X5.P$5; also elsewhere on the board
SIGNAL_ACCEL1: X5.P$25; also elsewhere on the board
SIGNAL_ACCEL2: X5.P$24; also elsewhere on the board
SIGNAL_BRAKE: X5.P$8; also elsewhere on the board
SIGNAL_CURRENT: X5.P$13; also elsewhere on the board

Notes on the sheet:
Pedals 5V
CANL for Motor Controller
Install resistors or LEDs here to limit current or drop voltage
Leonid Pozdneev
Board power distribution, connectors, and I/O.
